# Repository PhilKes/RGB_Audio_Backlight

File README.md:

# RGB Audio Backlight
* WS2812B RGB LED Stripe + Arduino Nano
* Switching modes via Button
* Tweaking mode settings via Potentiometer

## See Instructables for details:  [Instructable](https://www.instructables.com/id/RGB-Backlight-MSGEQ7-Audio-Visualizer/)

## Audio Visualizer with MSGEQ7 Hardware
[RGBStripe_MSGEQ7](/RGBStripe_FFT)

* MSGEQ7 Circuit connected to Arduino
* Audio Spectrum Analyzer using MSGEQ7 Band outputs

## Audio Visualizer with Fast Fourier Transformation (FFT)

* Audio Spectrum Analyzer only using Software ([fix_fft](https://www.arduinolibraries.info/libraries/fix_fft))

### Schematic

### 3D Printed Case

[RGBStripe_FFT](/RGBStripe_FFT)

* 3.5mm Aux connected to Analog Input of Arduino
* Audio Spectrum Analyzer using in Software FFT Algorithm to divide Signal in Audio Bands

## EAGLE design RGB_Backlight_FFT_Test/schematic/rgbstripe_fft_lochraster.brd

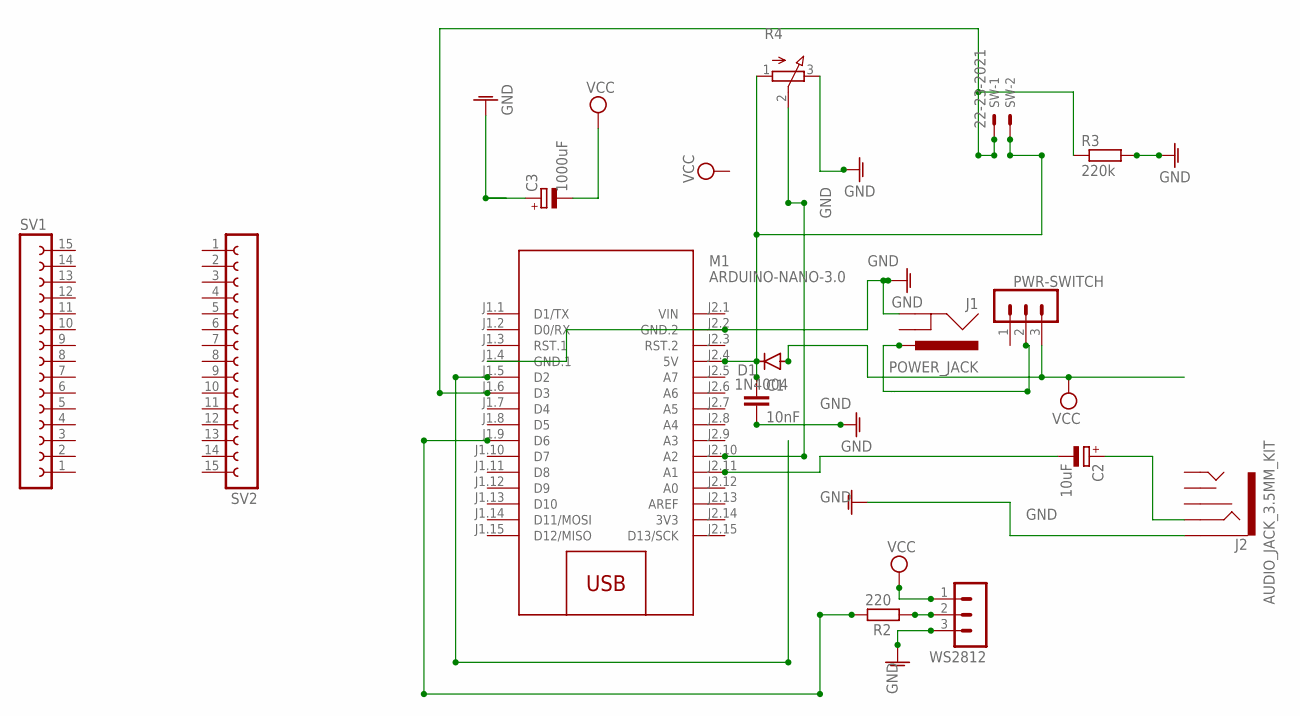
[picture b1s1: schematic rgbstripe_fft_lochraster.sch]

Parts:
C1: 10nF; C050-024X044
C2: 10uF; E2,5-6
C3: 1000uF; E3,5-8
D1: 1N4004; DO41-10
J1: POWER_JACK; POWER_JACK_PTH
J2: AUDIO_JACK_3.5MM_KIT; AUDIO-JACK-KIT
M1: ARDUINO-NANO-3.0
PWR-SWITCH: MA03-1
R2: 220; 0204/5
R3: 220k; 0204/7
R4: 3RP/1610N
SV1, SV2: FE15-1; FE15
SW: 22-23-2021
WS2812: MA03-1

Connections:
3V3: M1.J2.14 (3V3)
GND: C1.2, C3.+, J1.GND, J2.SLEEVE, M1.J1.4 (GND.1), M1.J2.2 (GND.2), R3.2, R4.3 (E), WS2812.3
unnamed: C1.1, D1.C, M1.J2.4 (5V), R4.1 (A), SW.2
unnamed: C2.+, J2.RING
unnamed: C2.-, M1.J2.11 (A1)
unnamed: M1.J1.9 (D6), R2.2
unnamed: M1.J2.10 (A2), R4.2 (S)
unnamed: R2.1, WS2812.2
unnamed: M1.J1.6 (D3), R3.1, SW.1
unnamed: J1.PWR, PWR-SWITCH.2
VCC: C3.-, D1.A, PWR-SWITCH.3, WS2812.1
VIN: M1.J2.1 (VIN)

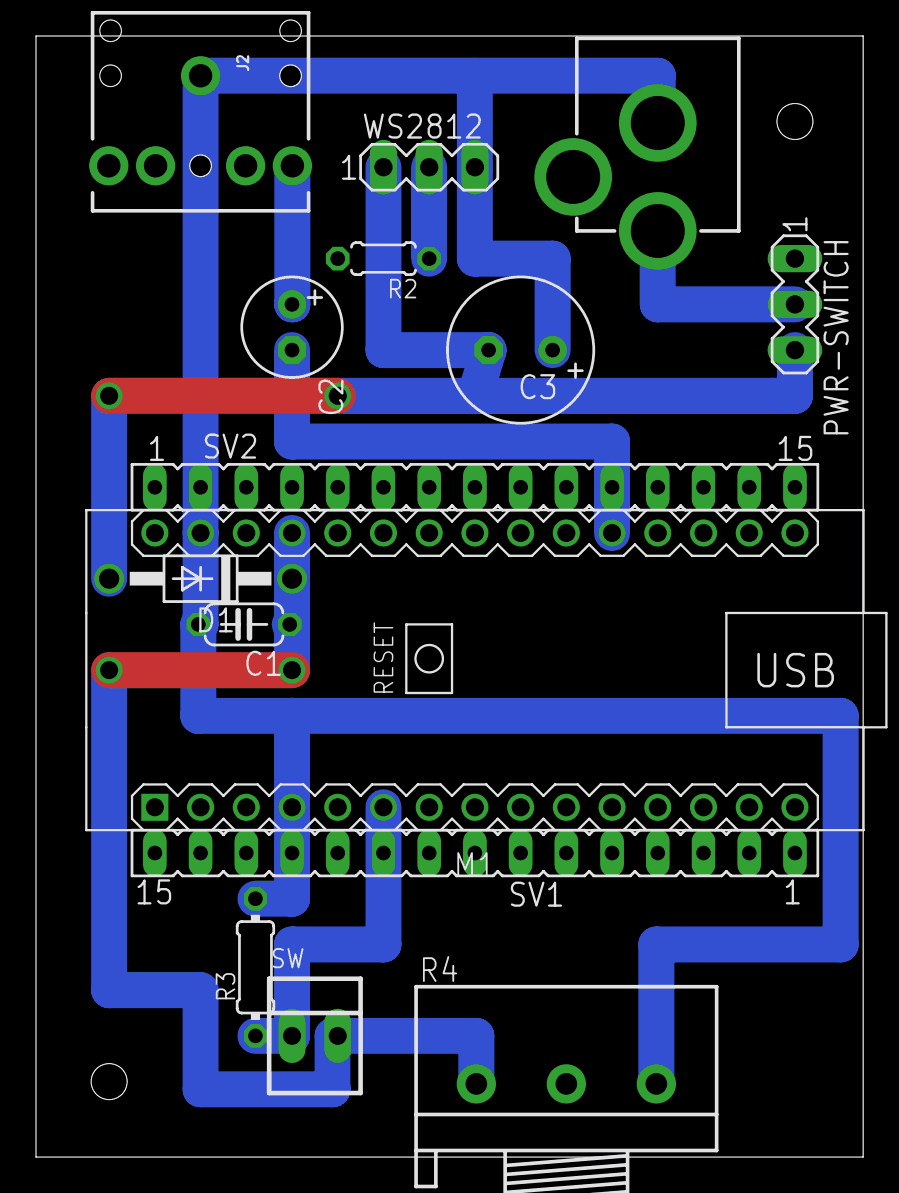
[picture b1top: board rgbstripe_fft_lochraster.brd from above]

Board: 2 copper layers, 46.0 x 62.3 mm, 15 parts (0 on the bottom side), 10 nets.

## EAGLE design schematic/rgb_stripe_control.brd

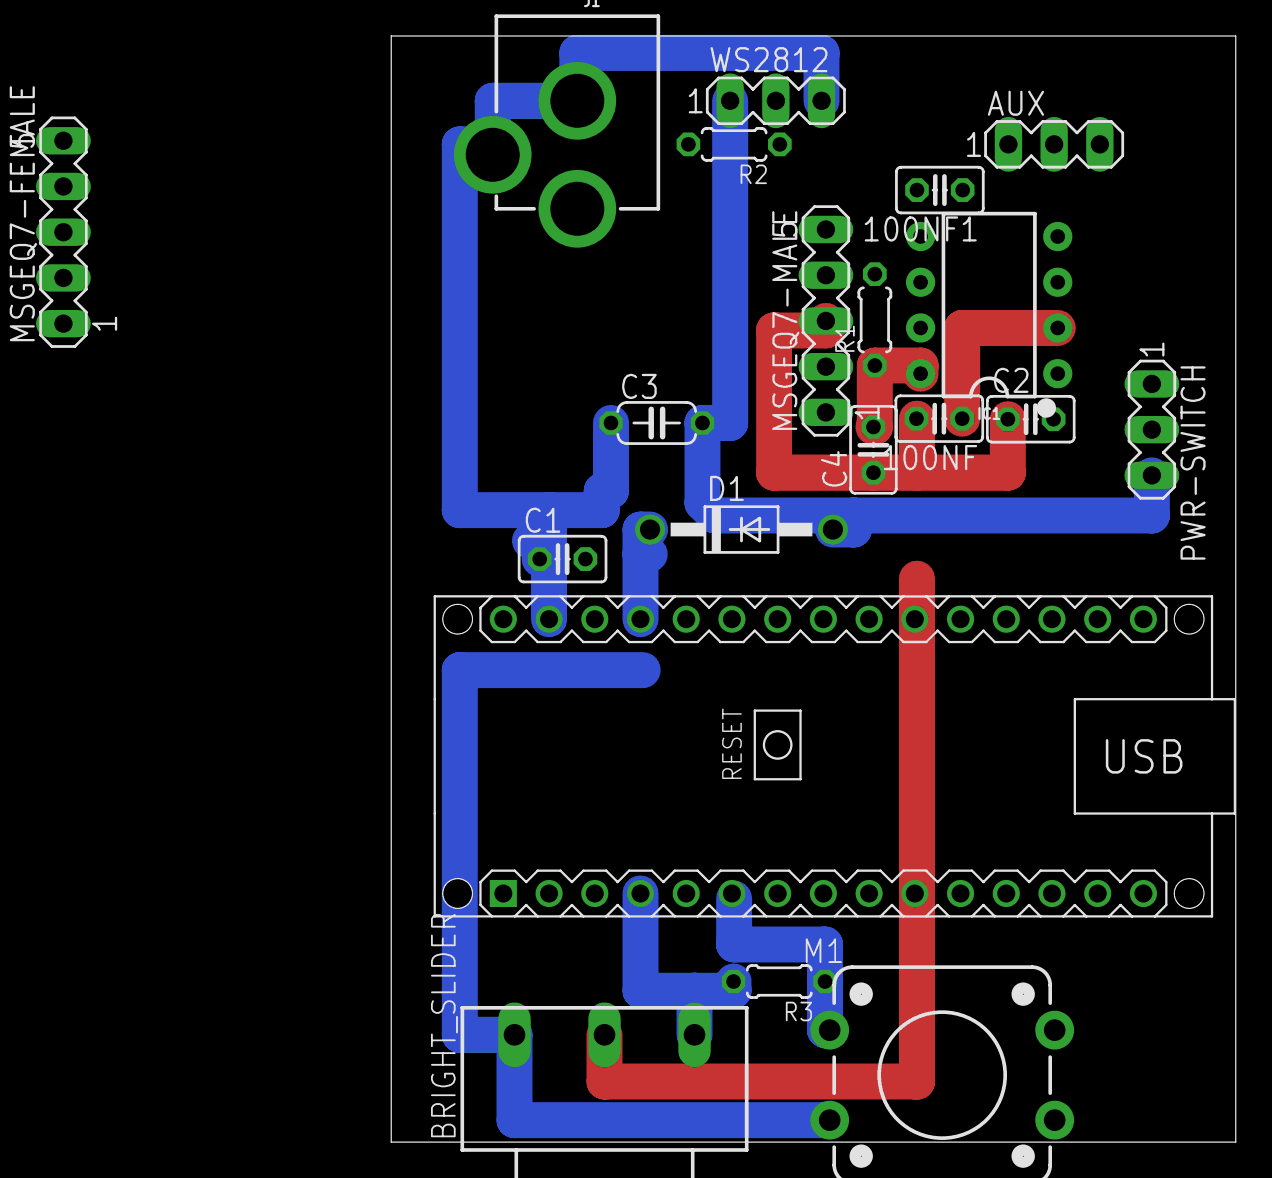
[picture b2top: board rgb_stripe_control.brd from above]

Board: 2 copper layers, 46.9 x 61.5 mm, 20 parts (0 on the bottom side), 20 nets.

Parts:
100NF: 33pF; C025-025X050
100NF1: 10nF; C025-025X050
AUX: MA03-1
BRIGHT_SLIDER: PC16S
C1: 10nF; C025-025X050
C2: 100nF; C025-025X050
C3: 1000uF; C050-024X044
C4: 33pF; C025-025X050
D1: 1N4004; DO41-10
IC1: MSGEQ7P; DIP08
J1: POWER_JACK; POWER_JACK_PTH
M1: ARDUINO-NANO-3.0
MSGEQ7-FEMALE, MSGEQ7-MALE: MA05-1
PWR-SWITCH: MA03-1
R1: 200k; 0204/5
R2: 220; 0204/5
R3: 10k; 0204/5
S1: MODE_SWITCH; TACTILE_SWITCH_PTH_12MM
WS2812: MA03-1

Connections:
GND: BRIGHT_SLIDER.1E, C1.1, C3.1, J1.GND, J1.GNDBREAK, M1.J1.4, M1.J2.2, MSGEQ7-FEMALE.3, R3.2, WS2812.3
unnamed: D1.C, M1.J2.4
unnamed: M1.J1.8, MSGEQ7-FEMALE.5
unnamed: M1.J2.11, MSGEQ7-FEMALE.2
unnamed: M1.J1.5, MSGEQ7-FEMALE.1
unnamed: C2.2, IC1.1, MSGEQ7-MALE.2, R1.2
unnamed: 100NF.2, C2.1, C4.1, IC1.6, MSGEQ7-MALE.3
unnamed: IC1.3, MSGEQ7-MALE.4
unnamed: IC1.4, MSGEQ7-MALE.5
unnamed: IC1.7, MSGEQ7-MALE.1
unnamed: 100NF1.1, AUX.1, AUX.2
unnamed: C4.2, IC1.8, R1.1
unnamed: 100NF.1, AUX.3, IC1.2
unnamed: 100NF1.2, IC1.5
unnamed: M1.J1.9, R2.2
unnamed: BRIGHT_SLIDER.1S, M1.J2.10
unnamed: R2.1, WS2812.2
unnamed: M1.J1.6, R3.1, S1.1
unnamed: J1.PWR, PWR-SWITCH.2
VCC: BRIGHT_SLIDER.1A, C1.2, C3.2, D1.A, MSGEQ7-FEMALE.4, PWR-SWITCH.3, S1.3, WS2812.1

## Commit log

2019-02-16 fixes
2019-02-26 fixed Interrupt
2019-03-10 added colorRoom
2019-03-16 added AudioVisulizer only
2020-08-05 schematic added
2020-08-15 added Sketch + Schematic using FFT instead of MSGEQ7 Circuit
2020-08-15 RGBStripe_MSGEQ7 added
2020-08-15 renamed Sketches
2020-08-15 FFT: added additional OLED_OUTPUT flag to enable debugging of Audio Bands
2020-08-20 case: 123Design case added + Sketches Updates
2020-08-29 FFT fixes
2020-09-02 finished 3D print case
2020-09-03 no message
2020-09-03 Sketch fixes
2020-09-03 Case fixes
2021-08-08 fix model .STL files
2023-11-22 Add LICENSE

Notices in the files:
parts and their libraries:
SparkFun-Connectors: Licensing: Creative Commons ShareAlike 4.0 International - https://creativecommons.org/licenses/by-sa/4.0
diy-modules-nano: Released under the Creative Commons Attribution 4.0 International License: http://creativecommons.org/licenses/by/4.0
